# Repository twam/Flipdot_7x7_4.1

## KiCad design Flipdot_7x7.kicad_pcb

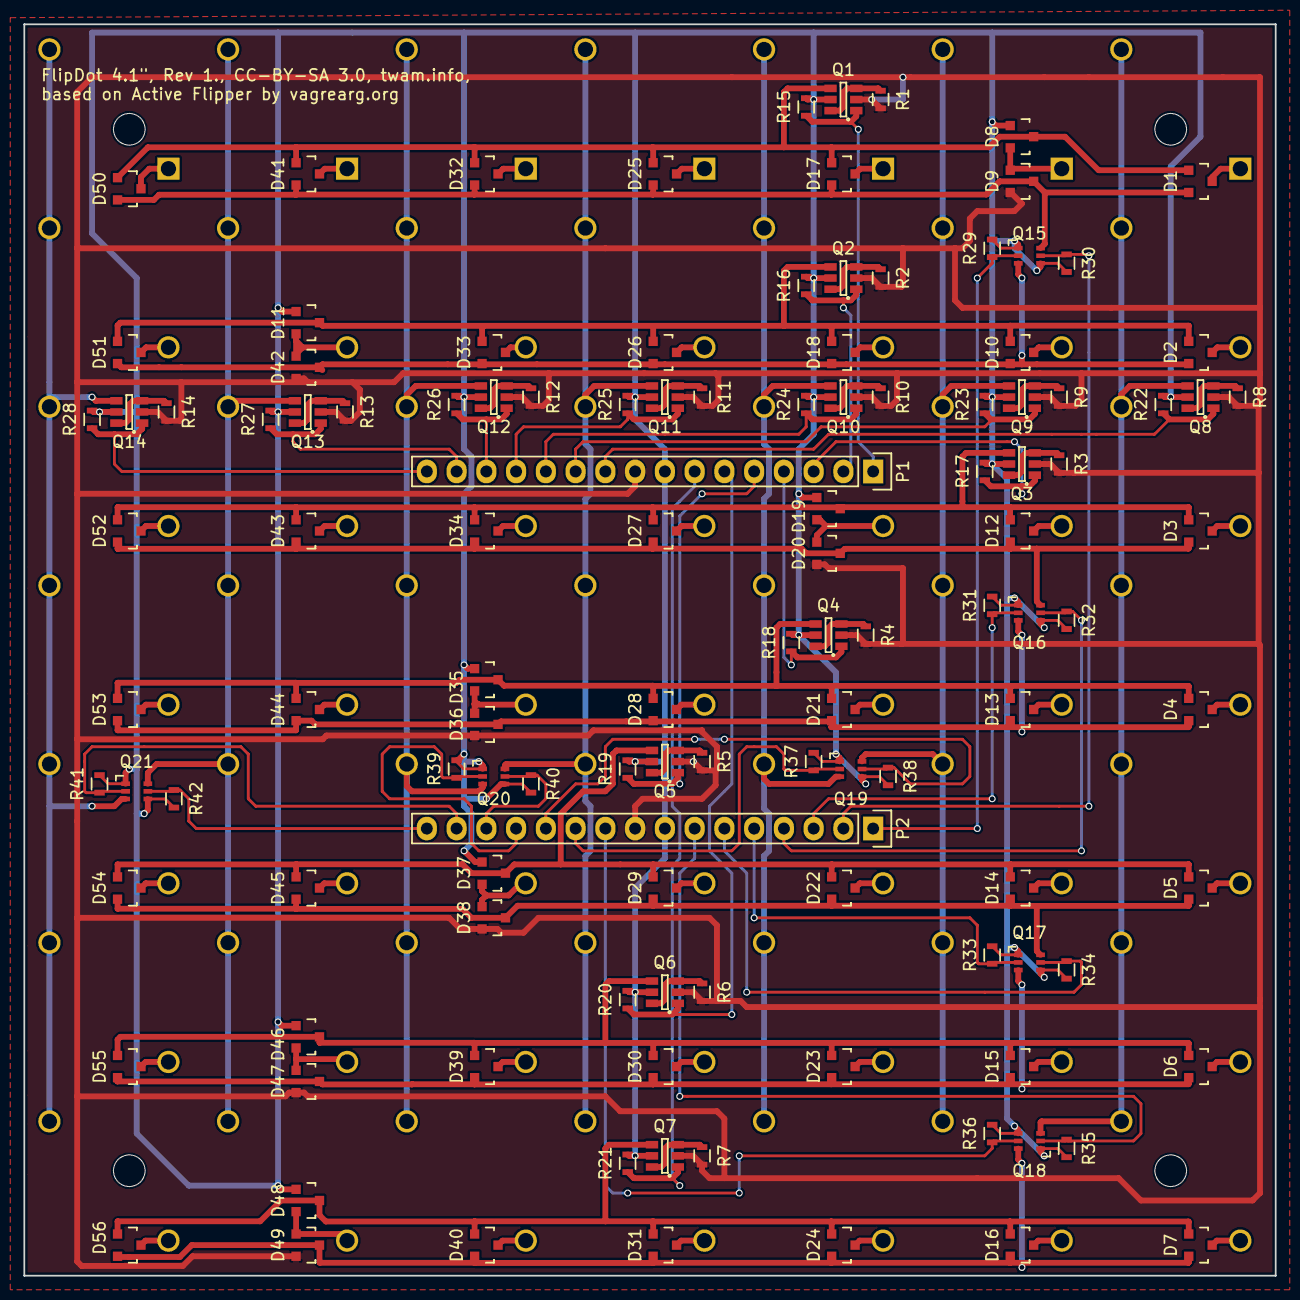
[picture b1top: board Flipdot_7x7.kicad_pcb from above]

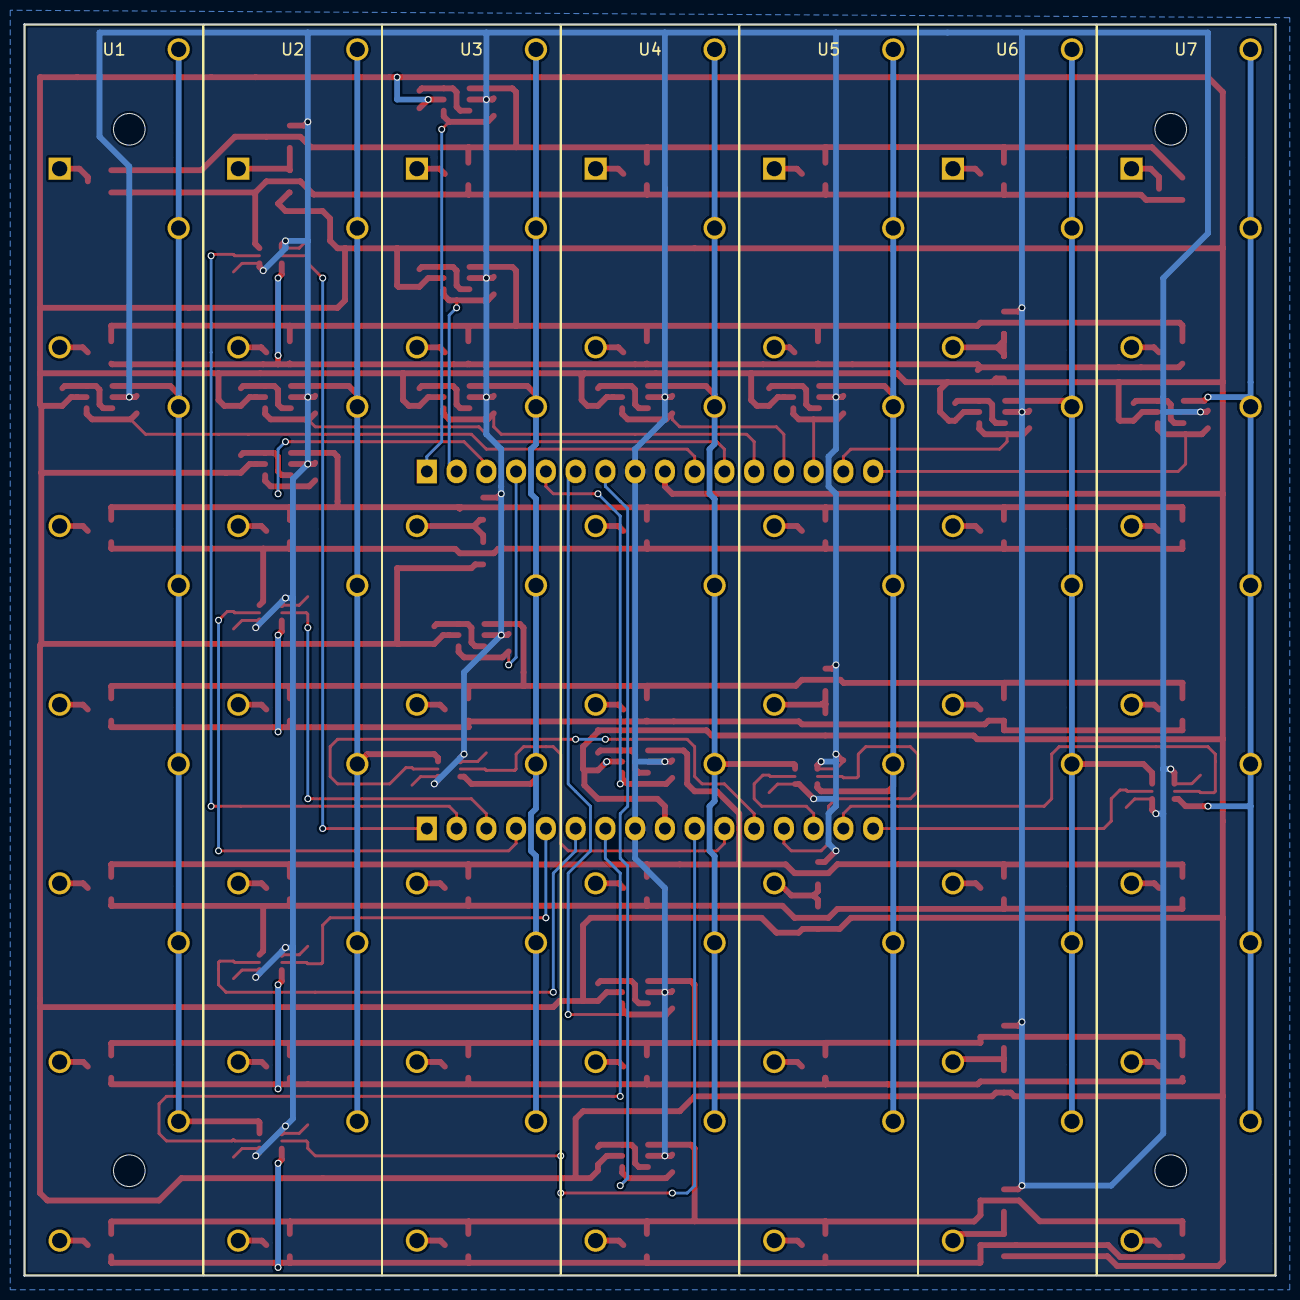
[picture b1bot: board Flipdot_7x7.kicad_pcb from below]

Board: 2 copper layers, 106.8 x 106.8 mm, 128 parts (7 on the bottom side), 114 nets.

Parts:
D1, D2, D3, D4, D5, D6, D7, D8, D9, D10, D11, D12, D13, D14, D15, D16, D17, D18, D19, D20, D21, D22, D23, D24, D25, D26, D27, D28, D29, D30, D31, D32, D33, D34, D35, D36, D37, D38, D39, D40, D41, D42, D43, D44, D45, D46, D47, D48, D49, D50, D51, D52, D53, D54, D55, D56: PMBD7000; SOT-23
P1, P2: CONN_01X16; Pin_Header_Straight_1x16
Q1, Q2, Q3, Q4, Q5, Q6, Q7, Q8, Q9, Q10, Q11, Q12, Q13, Q14: DMG6602SVT; SOT-23-6
Q15, Q16, Q17, Q18, Q19, Q20, Q21: DMN3190LDW; SC-70-6
R1, R2, R3, R4, R5, R6, R7, R8, R9, R10, R11, R12, R13, R14: 22k; R_0603
R15, R16, R17, R18, R19, R20, R21, R22, R23, R24, R25, R26, R27, R28, R29, R30, R31, R32, R33, R34, R35, R36, R37, R38, R39, R40, R41, R42: 100k; R_0603
U1, U2, U3, U4, U5, U6, U7: FlipDot; AZXY5_4.1

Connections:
/CH0: D1.1, D8.3, D17.1, D25.1, D32.1, D41.1, D50.1, Q1.4
/CH1: D2.1, D10.1, D11.3, D18.1, D26.1, D33.1, D51.1, Q2.4
/CH2: D3.1, D12.1, D19.3, D27.1, D34.1, D43.1, D52.1, Q3.4
/CH3: D4.1, D13.1, D21.1, D28.1, D35.3, D44.1, D53.1, Q4.4
/CH4: D5.1, D14.1, D22.1, D29.1, D37.3, D45.1, D54.1, Q5.4
/CH5: D6.1, D15.1, D23.1, D30.1, D39.1, D46.3, D55.1, Q6.4
/CH6: D7.1, D16.1, D24.1, D31.1, D40.1, D48.3, D56.1, Q7.4
/CHI0: P1.1, Q1.1, R15.1
/CHI1: P1.2, Q2.1, R16.1
/CHI2: P1.3, Q3.1, R17.1
/CHI3: P1.4, Q4.1, R18.1
/CHI4: P1.5, Q5.1, R19.1
/CHI5: P1.6, Q6.1, R20.1
/CHI6: P1.7, Q7.1, R21.1
/CL0: D1.2, D9.3, D17.2, D25.2, D32.2, D41.2, D50.2, Q15.6
/CL1: D2.2, D10.2, D18.2, D26.2, D33.2, D42.3, D51.2, Q15.3
/CL2: D3.2, D12.2, D20.3, D27.2, D34.2, D43.2, D52.2, Q16.6
/CL3: D4.2, D13.2, D21.2, D28.2, D36.3, D44.2, D53.2, Q16.3
/CL4: D5.2, D14.2, D22.2, D29.2, D38.3, D45.2, D54.2, Q17.6
/CL5: D6.2, D15.2, D23.2, D30.2, D39.2, D47.3, D55.2, Q17.3
/CL6: D7.2, D16.2, D24.2, D31.2, D40.2, D49.3, D56.2, Q18.6
/CLI0: P2.1, Q15.2, R29.1
/CLI1: P2.2, Q15.5, R30.1
/CLI2: P2.3, Q16.2, R31.1
/CLI3: P2.4, Q16.5, R32.1
/CLI4: P2.5, Q17.2, R33.1
/CLI5: P2.6, Q17.5, R34.1
/CLI6: P2.7, Q18.2, R35.1
/LS0: Q8.4, Q18.3, U1.8, U1.9, U1.10, U1.11, U1.12, U1.13, U1.14
/LS1: Q9.4, Q19.6, U2.8, U2.9, U2.10, U2.11, U2.12, U2.13, U2.14
/LS2: Q10.4, Q19.3, U3.8, U3.9, U3.10, U3.11, U3.12, U3.13, U3.14
/LS3: Q11.4, Q20.6, U4.8, U4.9, U4.10, U4.11, U4.12, U4.13, U4.14
/LS4: Q12.4, Q20.3, U5.8, U5.9, U5.10, U5.11, U5.12, U5.13, U5.14
/LS5: Q13.4, Q21.6, U6.8, U6.9, U6.10, U6.11, U6.12, U6.13, U6.14
/LS6: Q14.4, Q21.3, U7.8, U7.9, U7.10, U7.11, U7.12, U7.13, U7.14
/RHI0: P1.10, Q8.1, R22.1
/RHI1: P1.11, Q9.1, R23.1
/RHI2: P1.12, Q10.1, R24.1
/RHI3: P1.13, Q11.1, R25.1
/RHI4: P1.14, Q12.1, R26.1
/RHI5: P1.15, Q13.1, R27.1
/RHI6: P1.16, Q14.1, R28.1
/RLI0: P2.10, Q18.5, R36.1
/RLI1: P2.11, Q19.2, R37.1
/RLI2: P2.12, Q19.5, R38.1
/RLI3: P2.13, Q20.2, R39.1
/RLI4: P2.14, Q20.5, R40.1
/RLI5: P2.15, Q21.2, R41.1
/RLI6: P2.16, Q21.5, R42.1
GND: D8.1, D11.1, D19.1, D35.1, D37.1, D46.1, D48.1, P1.8, P2.8, Q1.5, Q2.5, Q3.5, Q4.5, Q5.5, Q6.5, Q7.5, Q8.5, Q9.5, Q10.5, Q11.5, Q12.5, Q13.5, Q14.5, Q15.1, Q15.4, Q16.1, Q16.4, Q17.1, Q17.4, Q18.1, Q18.4, Q19.1, Q19.4, Q20.1, Q20.4, Q21.1, Q21.4, R15.2, R16.2, R17.2, R18.2, R19.2, R20.2, R21.2, R22.2, R23.2, R24.2, R25.2, R26.2, R27.2, R28.2, R29.2, R30.2, R31.2, R32.2, R33.2, R34.2, R35.2, R36.2, R37.2, R38.2, R39.2, R40.2, R41.2, R42.2
unnamed: D1.3, U1.1
unnamed: D2.3, U1.2
unnamed: D3.3, U1.3
unnamed: D4.3, U1.4
unnamed: D5.3, U1.5
unnamed: D6.3, U1.6
unnamed: D7.3, U1.7
unnamed: D8.2, D9.1, U2.1
unnamed: D10.3, U2.2
unnamed: D11.2, D42.1, U6.2
unnamed: D12.3, U2.3
unnamed: D13.3, U2.4
unnamed: D14.3, U2.5
unnamed: D15.3, U2.6
unnamed: D16.3, U2.7
unnamed: D17.3, U3.1
unnamed: D18.3, U3.2
unnamed: D19.2, D20.1, U3.3
unnamed: D21.3, U3.4
unnamed: D22.3, U3.5
unnamed: D23.3, U3.6
unnamed: D24.3, U3.7
unnamed: D25.3, U4.1
unnamed: D26.3, U4.2
unnamed: D27.3, U4.3
unnamed: D28.3, U4.4
unnamed: D29.3, U4.5
unnamed: D30.3, U4.6
unnamed: D31.3, U4.7
unnamed: D32.3, U5.1
unnamed: D33.3, U5.2
unnamed: D34.3, U5.3
unnamed: D35.2, D36.1, U5.4
unnamed: D37.2, D38.1, U5.5
unnamed: D39.3, U5.6
unnamed: D40.3, U5.7
unnamed: D41.3, U6.1
unnamed: D43.3, U6.3
unnamed: D44.3, U6.4
unnamed: D45.3, U6.5
unnamed: D46.2, D47.1, U6.6
unnamed: D48.2, D49.1, U6.7
unnamed: D50.3, U7.1
unnamed: D51.3, U7.2
unnamed: D52.3, U7.3
unnamed: D53.3, U7.4
unnamed: D54.3, U7.5
unnamed: D55.3, U7.6
unnamed: D56.3, U7.7
unnamed: Q1.3, Q1.6, R1.2
unnamed: Q2.3, Q2.6, R2.2
unnamed: Q3.3, Q3.6, R3.2
unnamed: Q4.3, Q4.6, R4.2
unnamed: Q5.3, Q5.6, R5.2
unnamed: Q6.3, Q6.6, R6.2
unnamed: Q7.3, Q7.6, R7.2
unnamed: Q8.3, Q8.6, R8.2
unnamed: Q9.3, Q9.6, R9.2
unnamed: Q10.3, Q10.6, R10.2
unnamed: Q11.3, Q11.6, R11.2
unnamed: Q12.3, Q12.6, R12.2
unnamed: Q13.3, Q13.6, R13.2
unnamed: Q14.3, Q14.6, R14.2
VCC: D9.2, D20.2, D36.2, D38.2, D42.2, D47.2, D49.2, P1.9, P2.9, Q1.2, Q2.2, Q3.2, Q4.2, Q5.2, Q6.2, Q7.2, Q8.2, Q9.2, Q10.2, Q11.2, Q12.2, Q13.2, Q14.2, R1.1, R2.1, R3.1, R4.1, R5.1, R6.1, R7.1, R8.1, R9.1, R10.1, R11.1, R12.1, R13.1, R14.1

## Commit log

2016-04-24 Initial commit. Rev. 1

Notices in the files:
Flipdot_7x7.kicad_pcb:
License: CC-BY-SA 3.0
FlipDot 4.1\", Rev 1., CC-BY-SA 3.0, twam.info,
based on Active Flipper by vagrearg.org
